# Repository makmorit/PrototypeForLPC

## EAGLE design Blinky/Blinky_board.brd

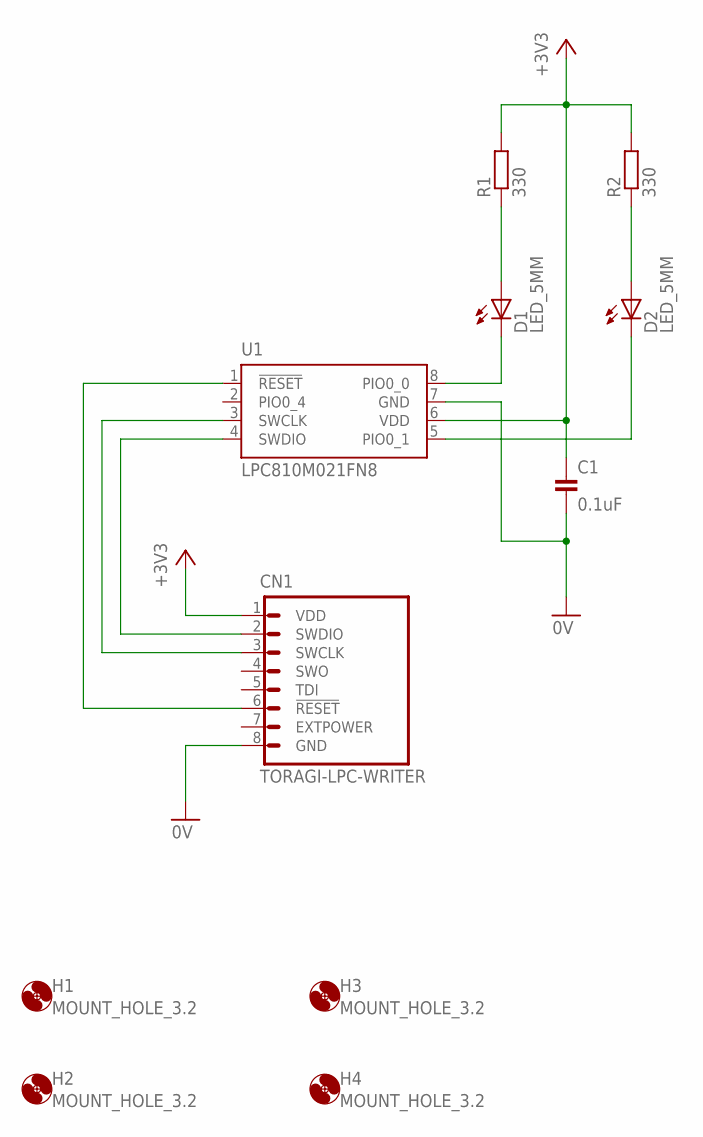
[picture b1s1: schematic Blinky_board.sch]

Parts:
C1: 0.1uF; CAP_100MIL
CN1: TORAGI-LPC-WRITER
D1, D2: LED_5MM; LED5MM
H1, H2, H3, H4: MOUNT_HOLE_3.2; 3,2
R1, R2: 330; RESISTOR_0204_200MIL
U1: LPC810M021FN8; DIL08

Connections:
0V: C1.2, CN1.8 (GND), U1.7 (GND)
+3V3: C1.1, CN1.1 (VDD), R1.2, R2.2, U1.6 (VDD)
unnamed: D1.A, R1.1
unnamed: D2.A, R2.1
unnamed: CN1.6 (!RESET!), U1.1 (!RESET!)
unnamed: CN1.2 (SWDIO), U1.4 (SWDIO)
unnamed: D2.K (C), U1.5 (PIO0_1)
unnamed: D1.K (C), U1.8 (PIO0_0)
unnamed: CN1.3 (SWCLK), U1.3 (SWCLK)

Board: 2 copper layers, 11 parts (0 on the bottom side), 9 nets, no tracks yet.

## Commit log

2017-05-06 LPC810用サンプルコード（Blinky）の初版
    必要最小限のコードだけを残すよう修正
    下記ライブラリーも合わせて登録（ノーカスタマイズ）
    ・CMSIS_CORE_LPC8xx
    ・lpc800_driver_lib
2017-05-06 LPC810用サンプル回路（Blinky）の初版
    デバッグ／電源供給に「トラ技ARMライタ」を使用する前提の回路図です。
2017-05-07 不要ファイルを削除
2017-05-07 LPC810用サンプルコード（Blinky）修正
    スイッチ押下で、点滅をストップ／リスタートさせる処理を追加
    スイッチ押下検知／連続押下検知抑止処理を追加
2017-05-07 LPC810用サンプル回路（Blinky）修正
    タクトスイッチを追加
2017-05-09 LPC810用サンプルコード（UART）の初版
2017-05-10 プロジェクト名を変更
    PIC側に合わせる（「ターゲット名_機能名」の形式）
2017-05-10 LPC810用サンプルコード（I2C）の初版
    温度センサー（STTS751）を接続して温度計測
    デバッガーで正しく計測できていることを確認済み。
